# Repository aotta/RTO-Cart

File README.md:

# RTO-Cart
Redesigned T-Cart - Multicart for Mattel Intellivision based on Teensy 4.1
It work with bin file loaded on sdcard, with ram/rom mapping from .cfg files with same name in same folder.
If found the [macro] section in the .cfg files, it ask for using the Cheat's pokes (middle button) or ignore them (other button).
File navigation is done with by buttons, while playing button 1 resets the console, button 3 resets the Cart.

You probably don't need mounting the resistor near the edge for reset the console, try yourself and be sure to have a good bipolar cap at reset line in your console! ;) 

More infor on:
https://forums.atariage.com/topic/346024-intellivision-rto-multicart-new-multicart/

User manual added by courtesy of Eskimo/RKOTower

Fixed version for SECAM Intellivision (thanks to zx81zx81):
https://github.com/zx81zx81/RTO-Cart-secam

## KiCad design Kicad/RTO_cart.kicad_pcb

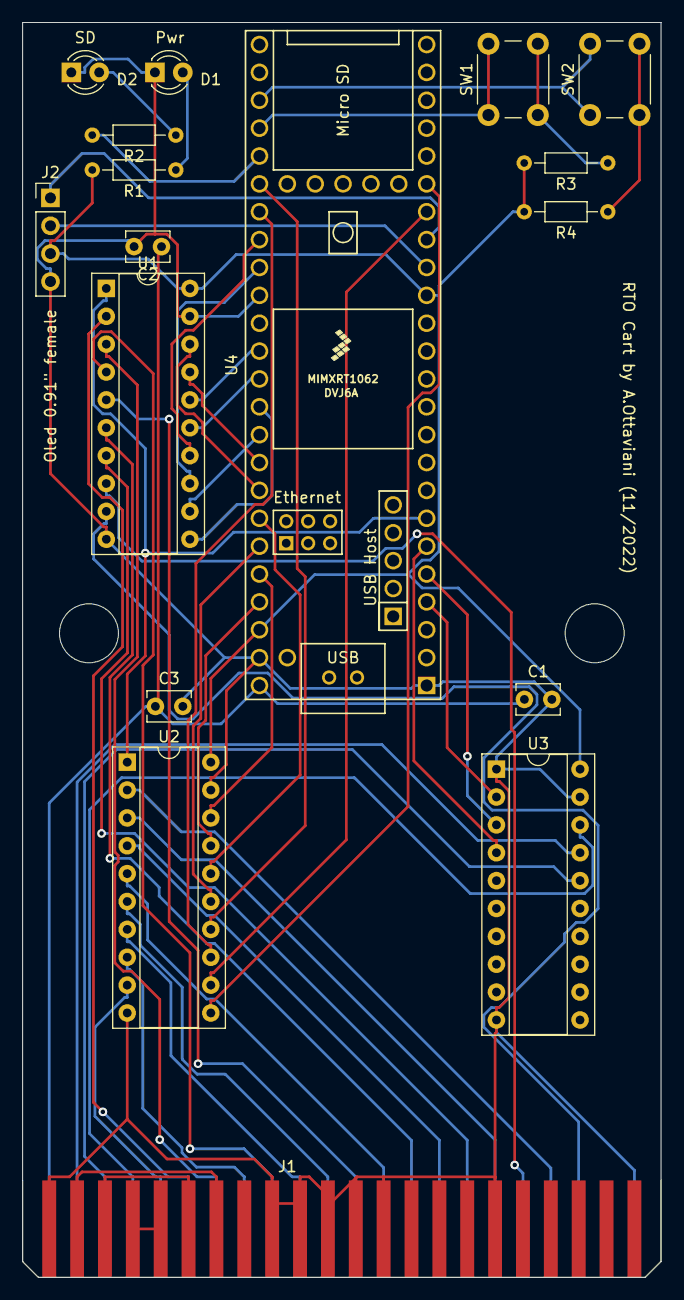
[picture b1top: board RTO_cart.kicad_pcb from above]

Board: 2 copper layers, 58.2 x 114.4 mm, 17 parts (0 on the bottom side), 54 nets.

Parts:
C1, C2, C3: 100nF; C_Disc_D3.8mm_W2.6mm_P2.50mm
D1, D2: LED; LED_D3.0mm
J1: 2x22 card edge connector; edge mounted 44 pin card edge connector (2x22 pin)
J2: Oled 0.91" female; PinHeader_1x04_P2.54mm_Vertical
R1, R2: R220; R_Axial_DIN0204_L3.6mm_D1.6mm_P7.62mm_Horizontal
R3, R4: 1K; R_Axial_DIN0204_L3.6mm_D1.6mm_P7.62mm_Horizontal
SW1, SW2: SW_Push; SW_PUSH_6mm
U1, U2, U3: 74LS245; DIP-20_W7.62mm_Socket
U4: Teensy4.1; Teensy41

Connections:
+3.3V: J2.3, R1.2, R3.2, R4.2, U1.20 (VCC), U2.20 (VCC), U3.20 (VCC), U4.15 (3V3), U4.46 (3V3)
+5V: C1.1, C2.1, C3.1, J1.43, U4.48 (VIN)
BC1: U3.3 (A1), U4.5 (3_LRCLK2)
BC2: U3.4 (A2), U4.6 (4_BCLK2)
BDIR: U3.2 (A0), U4.4 (2_OUT2)
BT1: SW1.1, U4.28 (36_CS)
BT2: SW2.1, U4.27 (35_TX8)
D0: U1.18 (B0), U4.41 (19_A5_SCL)
D1: U1.17 (B1), U4.40 (18_A4_SDA)
D2: U1.16 (B2), U4.36 (14_A0_TX3_SPDIF_OUT)
D3: U1.15 (B3), U4.37 (15_A1_RX3_SPDIF_IN)
D4: U1.14 (B4), U4.32 (40_A16)
D5: U1.13 (B5), U4.33 (41_A17)
D6: U1.12 (B6), U4.39 (17_A3_TX4_SDA1)
D7: U1.11 (B7), U4.38 (16_A2_RX4_SCL1)
D8: U2.18 (B0), U4.44 (22_A8_CTX1)
D9: U2.17 (B1), U4.45 (23_A9_CRX1_MCLK1)
D10: U2.16 (B2), U4.42 (20_A6_TX5_LRCLK1)
D11: U2.15 (B3), U4.43 (21_A7_RX5_BCLK1)
D12: U2.14 (B4), U4.30 (38_CS1_IN1)
D13: U2.13 (B5), U4.31 (39_MISO1_OUT1A)
D14: U2.12 (B6), U4.18 (26_A12_MOSI1)
D15: U2.11 (B7), U4.19 (27_A13_SCK1)
DIR: U1.1 (A->B), U2.1 (A->B), U4.7 (5_IN2)
GND: C1.2, C2.2, C3.2, D1.1 (K), D2.1 (K), J1.1, J1.12, J1.20, J1.22, J1.24, J1.26, J1.28, J1.44, J2.4, U1.10 (GND), U1.19 (CE), U2.10 (GND), U2.19 (CE), U3.1 (A->B), U3.10 (GND), U3.19 (CE), U4.1 (GND), U4.34 (GND), U4.47 (GND)
unnamed: D1.2 (A), R1.1
unnamed: D2.2 (A), R2.1
unnamed: J1.32, J1.42
unnamed: J1.34, J1.40
unnamed: J1.36, J1.38
unnamed: R3.1, SW1.2
unnamed: R4.1, SW2.2
SCL: J2.2, U4.16 (24_A10_TX6_SCL2)
SDA: J2.1, U4.17 (25_A11_RX6_SDA2)
Status: R2.2, U4.29 (37_CS)
bc1': J1.41, U3.17 (B1)
bc2': J1.39, U3.16 (B2)
bdir': J1.37, U3.18 (B0)
d0': J1.33, U1.2 (A0)
d1': J1.31, U1.3 (A1)
d2': J1.27, U1.4 (A2)
d3': J1.21, U1.5 (A3)
d4': J1.17, U1.6 (A4)
d5': J1.13, U1.7 (A5)
d6': J1.9, U1.8 (A6)
d7': J1.5, U1.9 (A7)
d8': J1.7, U2.2 (A0)
d9': J1.11, U2.3 (A1)
d10': J1.15, U2.4 (A2)
d11': J1.19, U2.5 (A3)
d12': J1.23, U2.6 (A4)
d13': J1.25, U2.7 (A5)
d14': J1.29, U2.8 (A6)
d15': J1.35, U2.9 (A7)

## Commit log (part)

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2022-11-13 Add files via upload
    first splash screen obtained!
2023-01-06 Add files via upload
    corrected the level shifter ICs to 74LVC245 instead of wrong typed 74LS245: WARNING! use only 74LVC245 chips, the other types could damage your Teensy becouse they output 5V instead of 3V3!
2023-01-07 Add files via upload
    changed bin file mapping. Waiting for an ECS to complete and test ;)
2023-01-07 added ECS bank switching support
2023-01-29 Create ver1.1a-beta
